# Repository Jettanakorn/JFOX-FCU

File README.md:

# JFOX FCU - Bare-Metal Rust Flight Controller

A bare-metal Rust firmware for the JFOX Flight Control Unit, targeting the
**PX4 FMUv2 board family** — `PX4FMUv2.4.5` and `Pixhawk 2.4.8` are revisions
of the same reference design and share this pin map.

**Verified on real Pixhawk 2.4.8 hardware (2026-08-04):** `jfox-fcu-usb`
flashes via QGroundControl, enumerates over USB, and QGC connects and holds the
link. Two things still vary across the family and are not settled by this
firmware — sensor population (2.4.8 clones may carry an ICM-20608/20602 rather
than an MPU-6000; `drivers::mpu6000` checks `WHO_AM_I` and fails loudly if so)
and silicon revision (which is why `memory.x` uses flash bank 1 only — see the
note there).

## Hardware

- **MCU**: STM32F427VIT6 (ARM Cortex-M4F @ 168MHz — see [Clock Configuration](#clock-configuration) for why not the part's 180MHz maximum)
- **Flash**: 2MB
- **RAM**: 256KB (192KB main + 64KB CCM)
- **IMU**: MPU-6000 (6-axis gyro + accel) @ 1kHz
- **Barometer**: MS5611
- **Storage**: FM25V01 FRAM (128Kbit)
- **Communication**: 4x UART, USB, CAN, I2C, SPI
- **I/O**: 8x PWM outputs

Schematic-level detail (connector pinouts, net traces) is in
**[`hardware/PX4FMUv2.4.5_NETS.md`](hardware/PX4FMUv2.4.5_NETS.md)**, derived
from the board's own Eagle netlist. The 3-board TMR array's KiCad project
lives in **[`hardware/`](hardware/README.md)**.

## Where things are

**Start here, depending on what you want to do:**

| I want to… | Read |
|---|---|
| Build firmware and get it onto a board | [`BUILD_AND_FLASH.md`](BUILD_AND_FLASH.md) |
| Bring up real hardware, 1 board → 3-board TMR | [`HARDWARE_BRINGUP.md`](HARDWARE_BRINGUP.md) |
| Work on the TMR schematic or carrier PCB | [`hardware/README.md`](hardware/README.md) |
| Understand the control law and its verification | [`docs/do178c/`](docs/do178c/) |
| Run the simulator | [`sitl/README.md`](sitl/README.md) |
| Know where a custom datalink would fit | [`JFOXGROUNDCONTROL_ROADMAP.md`](JFOXGROUNDCONTROL_ROADMAP.md) |

### Repository layout

```
jfox-fcu/
├── firmware/       # RTIC application - four [[bin]] targets, see BUILD_AND_FLASH.md
├── bsp/            # Board support: pin map, clock tree
├── hal/            # Register-level drivers: GPIO, SPI, UART, PWM, CAN, DWT
├── drivers/        # Sensors and storage: MPU-6000, FM25V01 FRAM
├── math/           # Vectors, quaternions, matrices, PID, filters
├── flight/         # Control law: fusion, stabilize, MPC, adaptive, redundancy, arming, BIT
├── telemetry/      # MAVLink v1 encoder
├── common/         # Types shared across crates without a dependency cycle
├── sitl/           # Host simulator - the real control chain against a 6-DOF plant
├── hardware/       # TMR schematic + carrier PCB (KiCad). Not built by cargo.
└── docs/
    ├── do178c/     # Requirements, traceability, coverage, coding standard
    ├── historical/ # Superseded 2025-12-30 docs and scripts - do not follow
    └── board-photos/
```

Two scripts live at the root because the flashing instructions call them
directly: `px4_flash_complete.py` (PX4-bootloader upload — the one with the
`GET_CRC` step the bootloader requires) and `px_mkfw.py` (vendored from PX4,
packages a `.bin` into the `.px4` format QGroundControl expects).

`memory.x` and `ccmram.x` are linker scripts; `Cargo.toml` is the workspace.

### Key Features

- **Pure bare-metal**: Direct register access, no HAL dependencies
- **RTIC framework**: Real-time task scheduling with zero-cost concurrency
- **Sensor fusion**: Madgwick AHRS filter @ 1kHz
- **Control loops**: Cascaded PID (attitude + rate) @ 500Hz
- **Safety**: Arming logic, failsafe, voltage monitoring

## Building

### Prerequisites

```bash
# Install Rust nightly
rustup default nightly
rustup target add thumbv7em-none-eabihf

# Install tools
cargo install probe-rs
```

### Build Firmware

```bash
cd firmware
cargo build --release
```

### Flash

```bash
# Via probe-rs (ST-Link/J-Link)
probe-rs run --chip STM32F427VITx \
  target/thumbv7em-none-eabihf/release/jfox-fcu

# Or use cargo alias
cargo rr
```

This project has more than one firmware binary (see `firmware/Cargo.toml`'s
`[[bin]]` entries) and a second flashing path (the board's built-in PX4
bootloader over USB, no debug probe needed) - see **[`BUILD_AND_FLASH.md`](BUILD_AND_FLASH.md)**
for the full picture, including current build/flash status per binary and
how to connect Mission Planner/QGroundControl.

## Task Architecture

| Task | Rate | Priority | Description |
|------|------|----------|-------------|
| `imu_task` | 1000 Hz | 3 (highest) | Read MPU-6000, run Madgwick filter |
| `control_task` | 500 Hz | 2 | Attitude/rate control with PID |
| `motor_task` | 400 Hz | 1 | PWM output to motors/servos |
| `heartbeat_task` | 1 Hz | 0 (idle) | Status LED blink |

## Clock Configuration

- **HSE**: 24MHz (external crystal)
- **PLL**: 24MHz / 12 × 168 / 2 = 168MHz
- **SYSCLK**: 168MHz
- **AHB (HCLK)**: 168MHz
- **APB1 (PCLK1)**: 42MHz
- **APB2 (PCLK2)**: 84MHz
- **USB 48MHz**: PLLQ = 336MHz VCO / 7 = 48MHz exactly

### Why 168MHz, not the part's 180MHz maximum

USB OTG FS needs 48MHz ±0.25%, and on STM32F42x/43x that clock can come
**only** from the main PLL's Q-output (PLL48CK). Unlike the F446/F469 and
F412/F413, this part has no `CK48MSEL` mux, so PLLSAI cannot feed USB.

180MHz needs a 360MHz VCO, and 360 has no integer PLLQ giving 48
(360/7.5). A 336MHz VCO does: 336/7 = 48 exactly, with PLLP=/2 giving
168MHz. Exact USB and 180MHz are mutually exclusive on this silicon, and
working USB was chosen over the extra 12MHz.

An earlier revision ran at 180MHz and tried to route PLLSAI to USB by
writing `CK48MSEL` at offset 0x90 — reserved space on this part, so the
write did nothing and USB ran from PLLQ at 360/7 ≈ 51.43MHz (7.1% fast).
Windows enumeration failed with "Configuration Descriptor Request Failed"
under a null VID/PID. `bsp/src/clocks.rs` carries the full note.

Anything clock-derived must be taken from `bsp::clocks` rather than
hardcoded — CAN bit timing and UART baud divisors in particular both
break silently if the clock tree moves and a stale literal is left behind.

## Memory Layout

- **Flash**: 0x08000000 - 0x081FFFFF (2MB)
- **RAM**: 0x20000000 - 0x2002FFFF (192KB)
- **CCMRAM**: 0x10000000 - 0x1000FFFF (64KB)
  - Core-Coupled Memory for zero wait-state access
  - Used for time-critical data (attitude, PID state)

## Sensor Configuration

### MPU-6000 (Primary IMU)
- **Interface**: SPI1 @ 5.625MHz
- **Gyro range**: ±2000 °/s
- **Accel range**: ±16g
- **Sample rate**: 1000 Hz
- **DLPF**: 184 Hz bandwidth

## Development Status

### ✅ Completed
- [x] Workspace structure and build system
- [x] Memory layout and clock configuration
- [x] GPIO and SPI HAL implementation
- [x] MPU-6000 driver with full initialization
- [x] Vector and quaternion math library
- [x] Madgwick AHRS sensor fusion
- [x] PID controller implementation
- [x] RTIC application with task scheduling
- [x] MAVLink v1 telemetry (`jfox-fcu-usb`: HEARTBEAT/SYS_STATUS/ATTITUDE,
      interim GCS bridge - see `BUILD_AND_FLASH.md`)

### 🚧 In Progress
- [ ] UART HAL for telemetry/GPS
- [ ] PWM output for motor control
- [ ] RC input (PPM/S.Bus/Spektrum)
- [ ] Motor mixer (quad/hexa/plane)

### 📋 Planned
- [ ] MS5611 barometer driver
- [ ] GPS integration (NMEA/UBX)
- [ ] Position hold and navigation
- [ ] DMA for efficient I/O
- [ ] Configuration storage in FRAM

## Pin Mapping

### SPI1 - MPU-6000
- SCK: PE13 (AF5)
- MISO: PE14 (AF5)
- MOSI: PE15 (AF5)
- CS: PC2 (GPIO)
- DRDY: PD15 (GPIO input)

### UART1 - Telemetry
- TX: PA9 (AF7)
- RX: PA10 (AF7)

### PWM Outputs
- CH1-4: TIM1 (PE9, PE11, PE13, PE14)
- CH5-8: TIM4 (PD12, PD13, PD14, PD15)

## Debugging

### View logs via defmt
```bash
probe-rs run --chip STM32F427VITx
```

### GDB debugging
```bash
# Terminal 1: Start GDB server
probe-rs gdb-server --chip STM32F427VITx

# Terminal 2: Connect GDB
arm-none-eabi-gdb target/thumbv7em-none-eabihf/release/jfox-fcu
(gdb) target remote :1337
(gdb) load
(gdb) continue
```

## Performance

| Metric | Target | Notes |
|--------|--------|-------|
| CPU usage | <60% | Leave headroom for future features |
| RAM usage | <128 KB | Half of available RAM |
| Flash usage | <1 MB | Half of available flash |
| IMU jitter | <1ms | Consistent 1kHz sampling |
| Control latency | <10ms | Sensor to motor output |

## Safety Features

1. **Pre-arm checks**: Sensor health, calibration valid
2. **Arming logic**: Explicit RC command required
3. **Failsafe**: RC loss → disarm or hold
4. **Low voltage**: Battery protection
5. **Watchdog**: Auto-reset on firmware hang
6. **Data validation**: CRC checks on sensor data

## License

MIT OR Apache-2.0

## Contributing

This is a reference implementation for bare-metal Rust flight controller development.
Contributions welcome!

## References

- [PX4 Autopilot](https://px4.io/)
- [Madgwick AHRS](https://x-io.co.uk/open-source-imu-and-ahrs-algorithms/)
- [RTIC Framework](https://rtic.rs/)
- [Embedded Rust Book](https://rust-embedded.github.io/book/)

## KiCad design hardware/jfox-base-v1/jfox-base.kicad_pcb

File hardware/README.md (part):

# hardware/ — TMR schematic work

Hardware design for the 3-board TMR array. Firmware lives everywhere else in
this repo; nothing here is compiled or linked into it.

## Why this directory exists

The only copy of the PX4FMUv2.4.5 schematic previously in this repo was
`docs/PX4FMUv2.4.5.pdf` — a vector PDF with **no extractable text**. Every
hardware fact taken from it had to be read off rendered page images by eye.
That is fine for orientation and bad as a foundation for a new board design.

The same design is published in machine-readable form: `PX4/Hardware`'s
`FMUv2/PX4FMUv2.4.5.sch`, Eagle 7.1.0 XML. The PDF is a plot of that file.
So connector pinouts and net membership are now **derived** from the netlist
rather than transcribed.

## Layout

| Path | What |
|---|---|
| `vendor/PX4FMUv2.4.5.sch` | Upstream Eagle source, unmodified. See `vendor/README.md`. |
| `tools/extract_eagle_nets.py` | Parses the above → `PX4FMUv2.4.5_NETS.md`. |
| `PX4FMUv2.4.5_NETS.md` | **Generated.** Connector/net reference. Do not hand-edit. |
| `tools/gen_tmr_schematic.py` | Emits the KiCad project below. |
| `jfox-tmr.kicad_pro` / `.kicad_sch` | **Generated.** Root: three FMU instances + carrier. |
| `fmu-v2/` | **Generated.** The real board, safe to instantiate 3x. |
| `carrier.kicad_sch` | **Generated.** The new carrier/backplane design. |
| `jfox.kicad_sym` / `sym-lib-table` | **Generated.** Connector symbols, registered as a project library. |
| `tools/check_tmr_netlist.py` | Asserts the redundancy invariants against KiCad's netlist. |
| `tools/gen_fmu_hierarchical.py` | Converts the import for safe 3× instantiation → `fmu-v2/`. |
| `tools/annotate_tmr_instances.py` | Gives each FMU instance its own reference designators. |
| `tools/check_fmu_conversion.py` | Proves the conversion changed no connectivity. |
| `tools/route_carrier.py` | Places the connectors and routes the carrier board. |

Full pipeline — regenerate and verify everything:

```bash
python hardware/tools/extract_eagle_nets.py
python hardware/tools/repair_import_hierarchy.py
python hardware/tools/gen_fmu_hierarchical.py
python hardware/tools/gen_tmr_schematic.py
python hardware/tools/annotate_tmr_instances.py
python hardware/tools/gen_carrier_pcb.py
#   ... then F8 in KiCad to load the netlist onto the board ...
python hardware/tools/route_carrier.py
python hardware/tools/check_fmu_conversion.py
python hardware/tools/check_tmr_netlist.py
```

Order matters: `annotate_tmr_instances.py` reads sheet UUIDs that
`gen_tmr_schematic.py` allocates, so it has to run after it.

(On this machine `python` on `PATH` is the Microsoft Store stub — use
`C:\Users\Jetta\AppData\Local\Programs\Python\Python312\python.exe`.)

## How to verify all of it

```bash
python hardware/tools/verify_all.py
```

Eight checks, each asking KiCad itself rather than the generators — the point
is to catch a generator that produced something plausible but wrong. Expect:

```
Imported FMU board
  [PASS] conversion preserved every connection  -- 262 nets in the import, 262 in the converted copy

3-board TMR system
  [PASS] every component has a unique designator  -- 885 instances, 885 distinct
  [PASS] the three supplies share no node
  [PASS] CAN_H reaches all three modules  -- via each module's own MAX3051
  [PASS] all three module terminators are on the bus  -- ['R409A', 'R409B', 'R409C']

Carrier board
  [PASS] DRC clean  -- 0 violations
  [PASS] fully routed  -- 0 unconnected
  [PASS] no net dead-ends on the board  -- 15 nets, all with a path across

all 8 checks passed
```

It exits non-zero on failure, and it is negative-tested: deleting a single
routed trace turns "fully routed" into `[FAIL] 1 unconnected`.

**Close KiCad before trusting a FAIL.** The script reads what is on disk; if
KiCad has unsaved changes the two disagree, and it prints a note when it sees
a lock file.

Everything here is saved in **KiCad 10** format. Each file type carries its own
version number — schematics `20260306`, boards `20260206`, symbol libraries
`20251024` — so those differing numbers are expected, not a mix of versions.
`gen_tmr_schematic.py` runs `kicad-cli sch upgrade` / `sym upgrade` on its
output, so opening the project does not rewrite anything.

### Looking at it by hand

| To see | Open |
|---|---|
| The board | `hardware/carrier/carrier.kicad_pro` → PCB editor |
| The carrier schematic | same project → schematic editor |
| The whole 3-board system | `hardware/jfox-tmr.kicad_pro` → schematic only |
| One module's real internals | `hardware/fmu-v2/fmu-v2.kicad_sch` (12 pages) |

In the TMR schematic, open the hierarchy navigator to move between `FMU-A`,
`FMU-B`, `FMU-C` and `CARRIER`. The three FMU sheets are the *same file* — a
change to one is a change to all three, which is the point.

## New board: JFOX-FMU v1

A ground-up replacement for the PX4FMUv2.4.5 modules - STM32H753 (Cortex-M7
@480 MHz, **1 MB RAM**), three IMUs per board, switchable CAN termination.
The v2.4.5 is a guideline only.

Specification: [`jfox-fmu-v1/ARCHITECTURE.md`](jfox-fmu-v1/ARCHITECTURE.md).
No schematic captured yet.

Note that the existing carrier PCB is built for v2.4.5's DF13 pinout and will
not fit the new module; it needs a redesign alongside. Its verified content -
CAN daisy chain, independent per-board power, no on-carrier termination -
carries over unchanged.

## Two projects, and why

| Project | What it is | Has a PCB? |
|---|---|---|
| `jfox-tmr.kicad_pro` | The **system** schematic — three FMU modules + the carrier, showing how the array is wired | **No, deliberately** |
| `carrier/carrier.kicad_pro` | The **board** — the only new hardware here | Yes |

Opening `jfox-tmr` and clicking **Switch to PCB Editor** pops up *"file does
not exist"* and offers to create one. **Say no.** That project has no board on
purpose: the three FMU modules are separately manufactured hardware, not parts
to be placed. A board made from that schematic would try to lay out ~885
components — three copies of a board that already exists. The same warning is
printed on the schematic's own root sheet.

The PCB is the carrier alone. Open `hardware/carrier/carrier.kicad_pro`.

## The TMR project

`jfox-tmr.kicad_sch` is the root. It instantiates **one** sheet file
(`fmu-v2/fmu-v2.kicad_sch`) three times as FMU-A/B/C — that is KiCad's own idiom for
identical repeated blocks, and it means editing the board design once edits
all three while KiCad still keeps their reference designators distinct via
per-instance paths.

Signal split, which is the load-bearing design decision:

- `CAN_H`, `CAN_L`, `GND`, `SAFETY` are **global labels** — correct precisely
  because all three boards genuinely share those nets.
- Power signals are **hierarchical pins**, so each board's stay
  separate. That separation is the entire point of board-level redundancy; a
  global label there would silently short all three supplies together.

That second point is the kind of mistake that looks fine in a schematic and
only shows up when hardware misbehaves, so it is checked mechanically.
`tools/check_tmr_netlist.py` runs `kicad-cli sch export netlist` and asserts,
against KiCad's own output:

- the three brick supplies share no node (independent power),
- `CAN_H`/`CAN_L` reach all three modules (one bus, not three stubs),
- **no resistor sits on CAN_H/CAN_L on the carrier** — each module already has
  a fixed 120Ω R409, and a fourth in parallel would make the bus worse,
- no net terminates on a single pin,
- `GND` is common across all modules.

Currently all five hold. Each check is negative-tested (deliberately merging
two supply nets, or dropping a module off the bus, both get caught).

## Status

**The Eagle import is done** (`PX4FMUv2.4.5/`) — 12 pages, 492 symbol
placements. Verified complete: the per-page symbol counts match an independent
parse of the Eagle source exactly, page for page
(23/36/24/32/49/69/45/49/58/24/49/34), and the exported netlist reproduces
`CAN_H`, `CAN_L`, `CAN1_TX` and `SAFETY` with the same nodes the Eagle netlist
has. No "Bus Entry needed" errors appeared.

**The import's root had to be repaired.** As it landed on disk, the container
root that referenced the 12 pages had been overwritten with page 1's own
content — its symbols carried instance path `/e0a7e50b…`, the UUID
`.kicad_pro` records as sheet `_1`, which is what a child page saved over its
parent looks like. KiCad consequently saw a **one-page project**: ERC
enumerated only `Sheet /`, and a netlist export returned 8 components instead
of ~292. The other 11 files were on disk, complete, and unreachable.

`tools/repair_import_hierarchy.py` rebuilds the container (moves page 1 to
`PX4FMUv2.4.5_1.kicad_sch`, writes a root holding the 12 sheet elements with
the UUIDs from `.kicad_pro` so existing instance paths still resolve) and then
verifies the result against the Eagle source. All 13 sheets now enumerate. Run
it again after any re-import; it is idempotent.

Note for anyone hand-editing these files: **instance-path forms differ between
KiCad versions and between these files.** KiCad 10 roots symbol paths at the
root document's UUID; KiCad 7 did not; the imported pages use a third form.
`annotate_tmr_instances.py` derives the prefix from the files rather than
assuming - assuming any one of them silently gave all three boards the same
reference designators.

### The global-label problem, and how it was fixed

The import represents every cross-page net as a **global** label — 136
distinct, 123 spanning multiple pages, no internal hierarchy at all. A global
label is global across the *whole project*, so instantiating this design three
times would have shorted all 120 non-shared nets together across FMU-A/B/C:
every SPI bus, every MCU pin, every internal rail. The schematic would have
looked completely normal and been electrically meaningless.

`tools/gen_fmu_hierarchical.py` generates `fmu-v2/` from the pristine import,
which it leaves untouched and re-importable:

- 120 multi-page nets → hierarchical labels plus matching sheet pins on a new
  container root, joined there by local labels. Connectivity is preserved but
  **scoped to one instance** of the board.
- 12 single-page nets → plain local labels; they never left the page.
- `CAN_H`, `CAN_L`, `GND`, `SAFETY` → left global, which is correct. They are
  the four nets the three modules genuinely share, and that is the same split
  the carrier assumes.
- `VDD_5V_BRICK`, `BATT_CURRENT_SENS`, `BATT_VOLTAGE_SENS` → also exposed on
  the root, so each board's power reaches its own carrier connector. (Those
  are the board's own net names; an earlier version of the TMR generator had
  invented `BATT_V_SENS`/`BATT_I_SENS`, which matched nothing.)

That is a lot of automated surgery on a design nobody can eyeball, so it is
checked rather than trusted. `tools/check_fmu_conversion.py` exports a netlist
from the pristine import and from the converted copy and compares them net by
net: **262 multi-pin nets on both sides, joining exactly the same pins.**

`tools/annotate_tmr_instances.py` then gives each instance its own reference
designators — `C101` becomes `C101A`/`C101B`/`C101C` — by writing one
`(path ...)` entry per instance, the same mechanism KiCad's own test project
uses for a thrice-instantiated subsheet. Without it all three boards report
the same designators and KiCad refuses to annotate.

## Installing KiCad

Current stable is **10.0.5** (released 2026-07-22). Install with:

```bash
winget install -e --id KiCad.KiCad
```

This is the x86-64 NSIS installer straight from KiCad's GitHub release.
Confirm it landed:

```bash
kicad-cli version
```

**Note the install location.** winget installs KiCad at *current-user* scope,
so it lands in `%LOCALAPPDATA%\Programs\KiCad\10.0\bin` — **not**
`C:\Program Files\KiCad`. Nothing is added to `PATH`, so either add that `bin`
directory or call the executable by full path.
`tools/check_tmr_netlist.py` probes both locations plus `PATH`.

**Why 10.x**, checked rather than assumed — KiCad 10's own docs list Eagle
(Autodesk) `.sch` XML, "Eagle version 6.x and later", among the supported
import formats, and `vendor/PX4FMUv2.4.5.sch` is Eagle 7.1.0. The docs also
confirm the importer extracts symbols from the file's embedded libraries into
a generated KiCad symbol library, which matches this file's seven embedded
libraries (`pixhawk2`, `con-hirose-df13`, `SparkFun`, …).

**Expect one Eagle-specific ERC violation.** KiCad documents a *"Bus Entry
needed"* error that "only applies to projects imported from EAGLE projects" —
places where the importer could not add bus entries automatically and you have
to place them by hand. Post-import cleanup, not a broken import.

**Verified with KiCad 10.0.5**: it parses all four files and resolves the
hierarchy — ERC enumerates `/`, `/FMU-A/`, `/FMU-B/`, `/FMU-C/` and
`/CARRIER/`, so the three-instance structure works. The netlist exports
cleanly and the invariants above hold.

ERC on the carrier reports **0 violations**. On the full TMR system it
reports 433, all inherited from the upstream board and its import - see
"System verification" above.

Two real defects were caught this way and fixed:

- **Symbol instance paths were wrong.** They used each child file's own UUID
  instead of `/<root-uuid>/<sheet-element-uuid>`. The files still parsed and
  the generator's structural checks still passed, but KiCad placed every
  carrier symbol on the root sheet. Only ERC surfaced it. The generator now
  checks instance-path rooting directly.
- **Symbols resolved to no registered library** (10 `lib_symbol_issues`
  warnings). Fixed by emitting a real `jfox.kicad_sym` plus a `sym-lib-table`.

## System verification

The whole point of the array is that three boards fail independently but vote
together. That is now demonstrable from KiCad's own netlist of
`jfox-tmr.kicad_sch`, not asserted:

- **885 component instances, 885 distinct references, 0 duplicated** — the
  three boards are genuinely separate instances, not one drawn three times.
- **The three supplies share no node.** `/VBRICK_A` reaches `C1101A`,
  `U1101A`, `J601A` and carrier `J4`/`J7`; `/VBRICK_B` reaches the `B` parts
  and `J5`/`J8`; `/VBRICK_C` the `C` parts and `J6`/`J9`. One brick failing
  cannot take the other two boards down.
- **CAN_H is one bus reaching all three modules' real hardware** — `U401A`,
  `U401B`, `U401C` (the MAX3051 transceivers), `R409A/B/C` (their fixed
  terminators), `J405A/B/C`, and the carrier's `J1`/`J2`/`J3`.

That last line is also the clearest statement of the R409 problem: three
terminators really are on one bus, so one of them really does have to come
off.

ERC on the full system reports **433 violations**, down from 1639 before the
conversion and library fixes. What remains is inherited from the upstream
board and its import, not introduced here: 363 `footprint_link_issues` (the
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
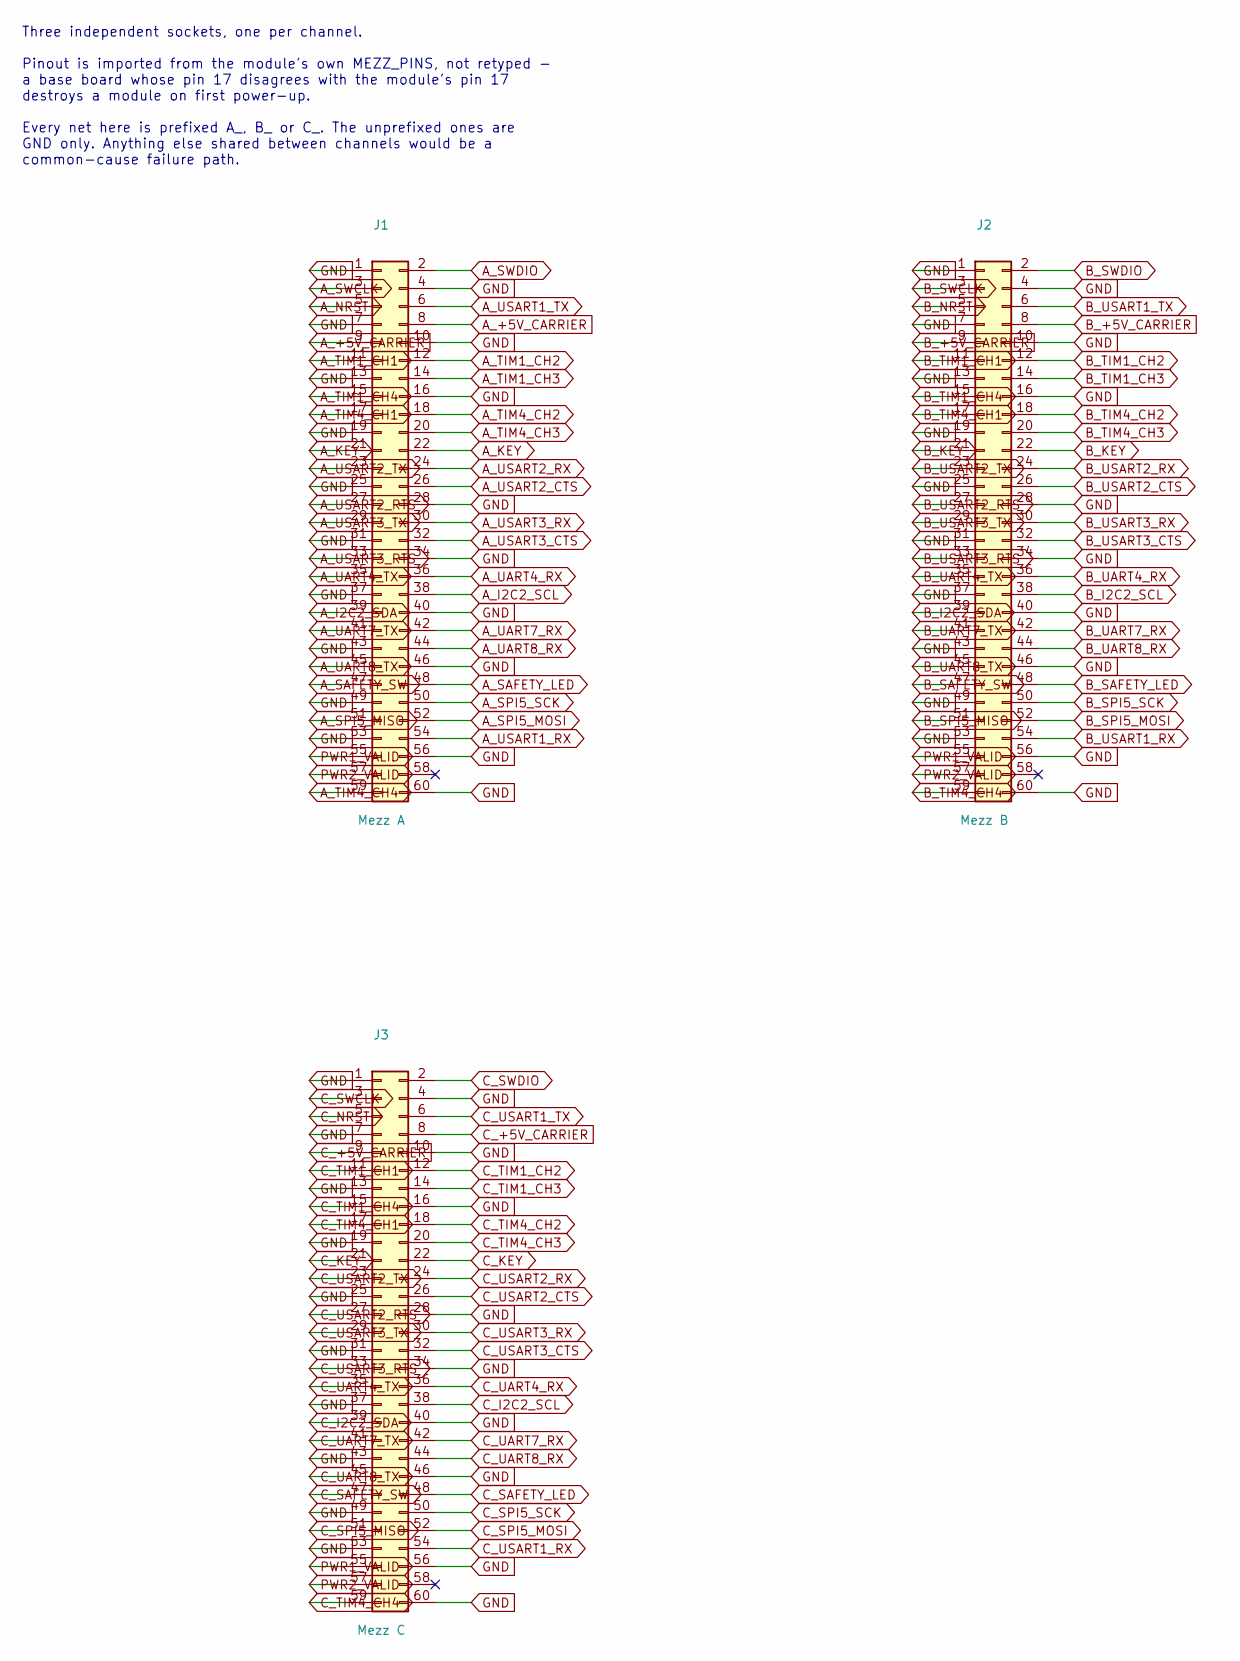
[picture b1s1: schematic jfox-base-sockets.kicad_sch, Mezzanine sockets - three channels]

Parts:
J1: Mezz A; Samtec_MECF-30-01-L-DV_2x30_P1.27mm_Polarized_Socket_Horizo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
J2: Mezz B; Samtec_MECF-30-01-L-DV_2x30_P1.27mm_Polarized_Socket_Horizo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
J3: Mezz C; Samtec_MECF-30-01-L-DV_2x30_P1.27mm_Polarized_Socket_Horizo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

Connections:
A_+5V_CARRIER: J1.8, J1.9; also elsewhere on the board
A_I2C2_SCL: J1.38; also elsewhere on the board
A_I2C2_SDA: J1.39; also elsewhere on the board
A_NRST: J1.5; also elsewhere on the board
A_SAFETY_LED: J1.48; also elsewhere on the board
A_SAFETY_SW: J1.47; also elsewhere on the board
A_SPI5_MISO: J1.51; also elsewhere on the board
A_SPI5_MOSI: J1.52; also elsewhere on the board
A_SPI5_SCK: J1.50; also elsewhere on the board
A_SWCLK: J1.3; also elsewhere on the board
A_SWDIO: J1.2; also elsewhere on the board
A_TIM1_CH1: J1.11; also elsewhere on the board
A_TIM1_CH2: J1.12; also elsewhere on the board
A_TIM1_CH3: J1.14; also elsewhere on the board
A_TIM1_CH4: J1.15; also elsewhere on the board
A_TIM4_CH1: J1.17; also elsewhere on the board
A_TIM4_CH2: J1.18; also elsewhere on the board
A_TIM4_CH3: J1.20; also elsewhere on the board
A_TIM4_CH4: J1.59; also elsewhere on the board
A_UART4_RX: J1.36; also elsewhere on the board
A_UART4_TX: J1.35; also elsewhere on the board
A_UART7_RX: J1.42; also elsewhere on the board
A_UART7_TX: J1.41; also elsewhere on the board
A_UART8_RX: J1.44; also elsewhere on the board
A_UART8_TX: J1.45; also elsewhere on the board
A_USART1_RX: J1.54; also elsewhere on the board
A_USART1_TX: J1.6; also elsewhere on the board
A_USART2_CTS: J1.26; also elsewhere on the board
A_USART2_RTS: J1.27; also elsewhere on the board
A_USART2_RX: J1.24; also elsewhere on the board
A_USART2_TX: J1.23; also elsewhere on the board
A_USART3_CTS: J1.32; also elsewhere on the board
A_USART3_RTS: J1.33; also elsewhere on the board
A_USART3_RX: J1.30; also elsewhere on the board
A_USART3_TX: J1.29; also elsewhere on the board
B_+5V_CARRIER: J2.8, J2.9; also elsewhere on the board
B_I2C2_SCL: J2.38; also elsewhere on the board
B_I2C2_SDA: J2.39; also elsewhere on the board
B_NRST: J2.5; also elsewhere on the board
B_SAFETY_LED: J2.48; also elsewhere on the board
B_SAFETY_SW: J2.47; also elsewhere on the board
B_SPI5_MISO: J2.51; also elsewhere on the board
B_SPI5_MOSI: J2.52
B_SPI5_SCK: J2.50; also elsewhere on the board
B_SWCLK: J2.3; also elsewhere on the board
B_SWDIO: J2.2; also elsewhere on the board
B_TIM1_CH1: J2.11; also elsewhere on the board
B_TIM1_CH2: J2.12; also elsewhere on the board
B_TIM1_CH3: J2.14; also elsewhere on the board
B_TIM1_CH4: J2.15; also elsewhere on the board
B_TIM4_CH1: J2.17; also elsewhere on the board
B_TIM4_CH2: J2.18; also elsewhere on the board
B_TIM4_CH3: J2.20; also elsewhere on the board
B_TIM4_CH4: J2.59; also elsewhere on the board
B_UART4_RX: J2.36; also elsewhere on the board
B_UART4_TX: J2.35; also elsewhere on the board
B_UART7_RX: J2.42; also elsewhere on the board
B_UART7_TX: J2.41; also elsewhere on the board
B_UART8_RX: J2.44; also elsewhere on the board
B_UART8_TX: J2.45; also elsewhere on the board
B_USART1_RX: J2.54
B_USART1_TX: J2.6; also elsewhere on the board
B_USART2_CTS: J2.26; also elsewhere on the board
B_USART2_RTS: J2.27; also elsewhere on the board
B_USART2_RX: J2.24; also elsewhere on the board
B_USART2_TX: J2.23; also elsewhere on the board
B_USART3_CTS: J2.32; also elsewhere on the board
B_USART3_RTS: J2.33; also elsewhere on the board
B_USART3_RX: J2.30; also elsewhere on the board
B_USART3_TX: J2.29; also elsewhere on the board
C_+5V_CARRIER: J3.8, J3.9; also elsewhere on the board
C_I2C2_SCL: J3.38; also elsewhere on the board
C_I2C2_SDA: J3.39; also elsewhere on the board
C_NRST: J3.5; also elsewhere on the board
C_SAFETY_LED: J3.48; also elsewhere on the board
C_SAFETY_SW: J3.47; also elsewhere on the board
C_SPI5_MISO: J3.51; also elsewhere on the board
C_SPI5_MOSI: J3.52
C_SPI5_SCK: J3.50; also elsewhere on the board
C_SWCLK: J3.3; also elsewhere on the board
C_SWDIO: J3.2; also elsewhere on the board
C_TIM1_CH1: J3.11; also elsewhere on the board
C_TIM1_CH2: J3.12; also elsewhere on the board
C_TIM1_CH3: J3.14; also elsewhere on the board
C_TIM1_CH4: J3.15; also elsewhere on the board
C_TIM4_CH1: J3.17; also elsewhere on the board
C_TIM4_CH2: J3.18; also elsewhere on the board
C_TIM4_CH3: J3.20; also elsewhere on the board
C_TIM4_CH4: J3.59; also elsewhere on the board
C_UART4_RX: J3.36; also elsewhere on the board
C_UART4_TX: J3.35; also elsewhere on the board
C_UART7_RX: J3.42; also elsewhere on the board
C_UART7_TX: J3.41; also elsewhere on the board
C_UART8_RX: J3.44; also elsewhere on the board
C_UART8_TX: J3.45; also elsewhere on the board
C_USART1_RX: J3.54
C_USART1_TX: J3.6; also elsewhere on the board
C_USART2_CTS: J3.26; also elsewhere on the board
C_USART2_RTS: J3.27; also elsewhere on the board
C_USART2_RX: J3.24; also elsewhere on the board
C_USART2_TX: J3.23; also elsewhere on the board
C_USART3_CTS: J3.32; also elsewhere on the board
C_USART3_RTS: J3.33; also elsewhere on the board
C_USART3_RX: J3.30; also elsewhere on the board
C_USART3_TX: J3.29; also elsewhere on the board
GND: J1.1, J1.4, J1.7, J1.10, J1.13, J1.16, J1.19, J1.25, J1.28, J1.31, J1.34, J1.37, J1.40, J1.43, J1.46, J1.49, J1.53, J1.56, J1.60, J2.1, J2.4, J2.7, J2.10, J2.13, J2.16, J2.19, J2.25, J2.28, J2.31, J2.34, J2.37, J2.40, J2.43, J2.46, J2.49, J2.53, J2.56, J2.60, J3.1, J3.4, J3.7, J3.10, J3.13, J3.16, J3.19, J3.25, J3.28, J3.31, J3.34, J3.37, J3.40, J3.43, J3.46, J3.49, J3.53, J3.56, J3.60; also elsewhere on the board
PWR1_VALID: J1.55, J2.55, J3.55; also elsewhere on the board
PWR2_VALID: J1.57, J2.57, J3.57; also elsewhere on the board

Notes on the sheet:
Three independent sockets, one per channel. Pinout is imported from the module's own MEZZ_PINS, not retyped - a base board whose pin 17 disagrees with the module's pin 17 destroys a module on first power-up. Every net here is prefixed A_, B_ or C_. The unprefixed ones are GND only. Anything else sh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

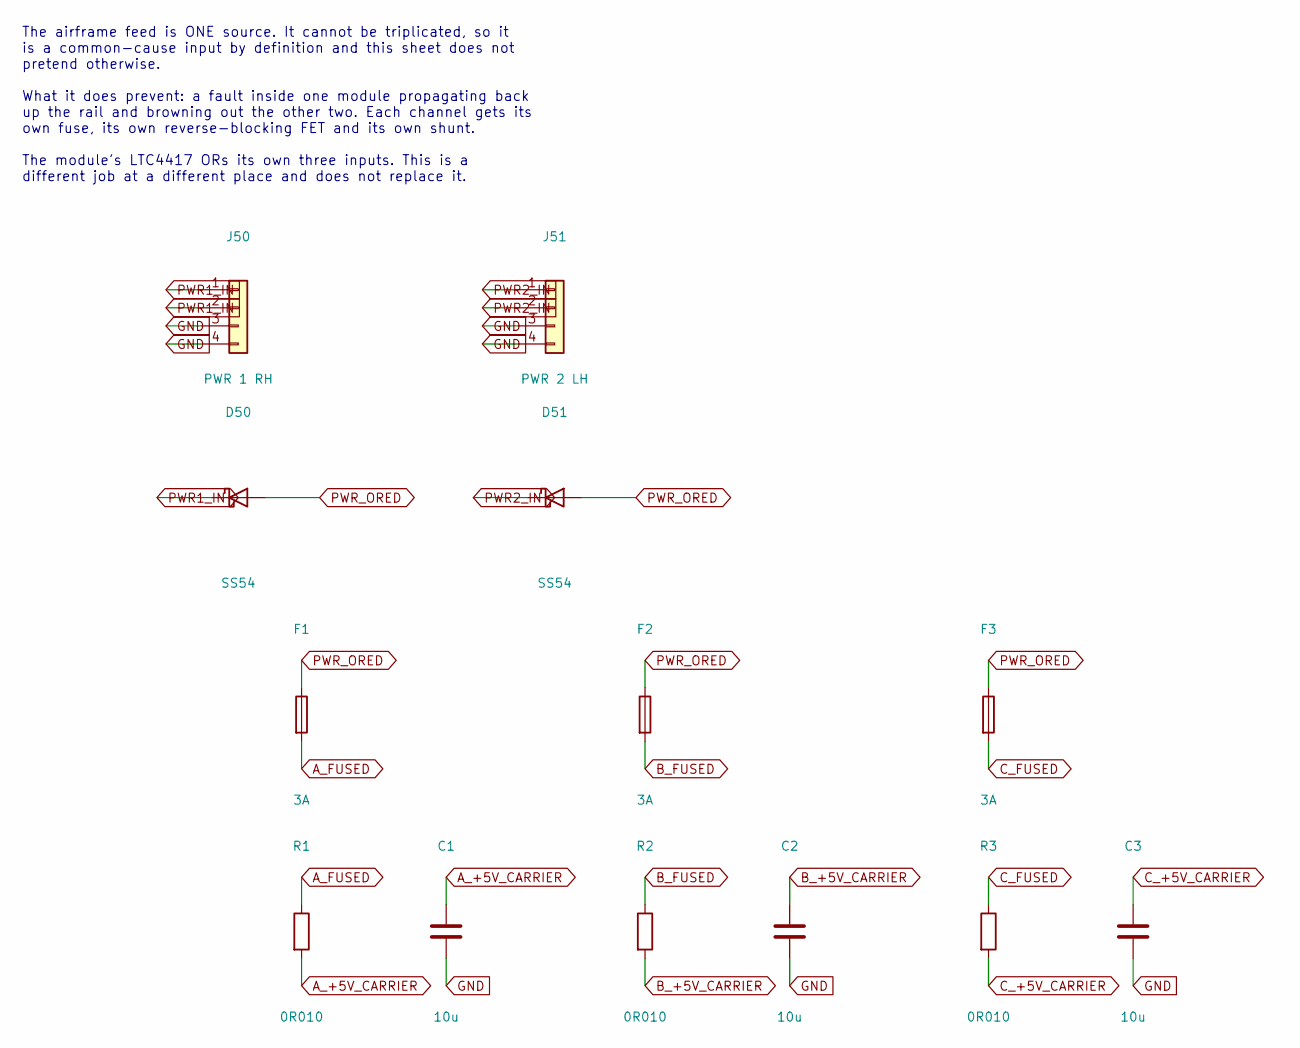
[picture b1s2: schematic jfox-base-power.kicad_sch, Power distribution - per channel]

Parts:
C1, C2, C3: 10u; C_0805_2012Metric
D50, D51: SS54; D_SMA
F1, F2, F3: 3A; Fuse_1206_3216Metric
J50: PWR 1 RH; JST_GH_SM04B-GHS-TB_1x04-1MP_P1.25mm_Horizontal
J51: PWR 2 LH; JST_GH_SM04B-GHS-TB_1x04-1MP_P1.25mm_Horizontal
R1, R2, R3: 0R010; R_0402_1005Metric

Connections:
A_+5V_CARRIER: C1.1, R1.2; also elsewhere on the board
A_FUSED: F1.2, R1.1
B_+5V_CARRIER: C2.1, R2.2; also elsewhere on the board
B_FUSED: F2.2, R2.1
C_+5V_CARRIER: C3.1, R3.2; also elsewhere on the board
C_FUSED: F3.2, R3.1
GND: C1.2, C2.2, C3.2, J50.3, J50.4, J51.3, J51.4; also elsewhere on the board
PWR_ORED: D50.2 (A), D51.2 (A), F1.1, F2.1, F3.1; also elsewhere on the board

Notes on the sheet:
The airframe feed is ONE source. It cannot be triplicated, so it is a common-cause input by definition and this sheet does not pretend otherwise. What it does prevent: a fault inside one module propagating back up the rail and browning out the other two. Each channel gets its own fuse, its own reve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

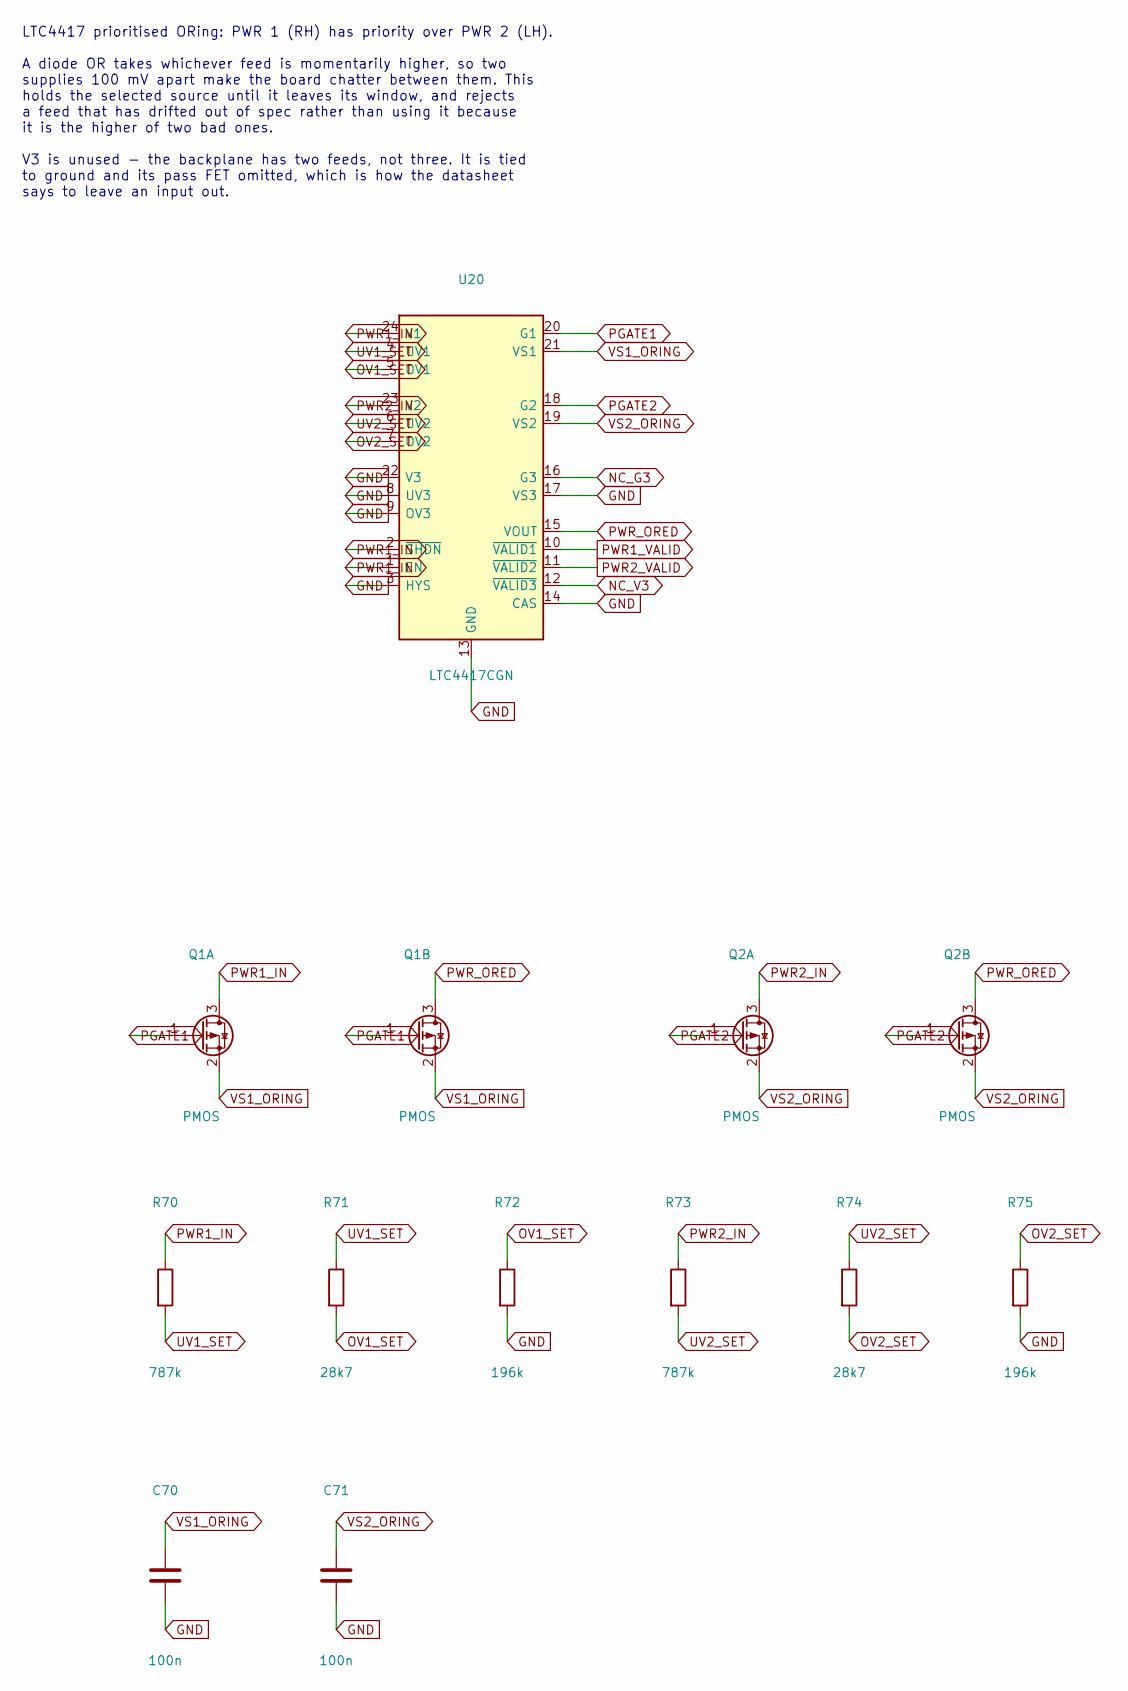
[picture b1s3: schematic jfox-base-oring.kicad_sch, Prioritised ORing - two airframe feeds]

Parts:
C70, C71: 100n; C_0402_1005Metric
Q1A, Q1B, Q2A, Q2B: PMOS; SOT-23
R70, R73: 787k; R_0402_1005Metric
R71, R74: 28k7; R_0402_1005Metric
R72, R75: 196k; R_0402_1005Metric
U20: LTC4417CGN; SSOP-24_3.9x8.7mm_P0.635mm

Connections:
GND: C70.2, C71.2, R72.2, R75.2, U20.3 (HYS), U20.8 (UV3), U20.9 (OV3), U20.13 (GND), U20.14 (CAS), U20.17 (VS3), U20.22 (V3); also elsewhere on the board
NC_G3: U20.16 (G3)
NC_V3: U20.12 (~VALID3)
OV1_SET: R71.2, R72.1, U20.5 (OV1)
OV2_SET: R74.2, R75.1, U20.7 (OV2)
PGATE1: Q1A.1 (G), Q1B.1 (G), U20.20 (G1)
PGATE2: Q2A.1 (G), Q2B.1 (G), U20.18 (G2)
PWR1_VALID: U20.10 (~VALID1); also elsewhere on the board
PWR2_VALID: U20.11 (~VALID2); also elsewhere on the board
PWR_ORED: Q1B.3 (D), Q2B.3 (D), U20.15 (VOUT); also elsewhere on the board
UV1_SET: R70.2, R71.1, U20.4 (UV1)
UV2_SET: R73.2, R74.1, U20.6 (UV2)
VS1_ORING: C70.1, Q1A.2 (S), Q1B.2 (S), U20.21 (VS1)
VS2_ORING: C71.1, Q2A.2 (S), Q2B.2 (S), U20.19 (VS2)

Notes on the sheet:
LTC4417 prioritised ORing: PWR 1 (RH) has priority over PWR 2 (LH). A diode OR takes whichever feed is momentarily higher, so two supplies 100 mV apart make the board chatter between them. This holds the selected source until it leaves its window, and rejects a feed that has drifted out of spec rat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

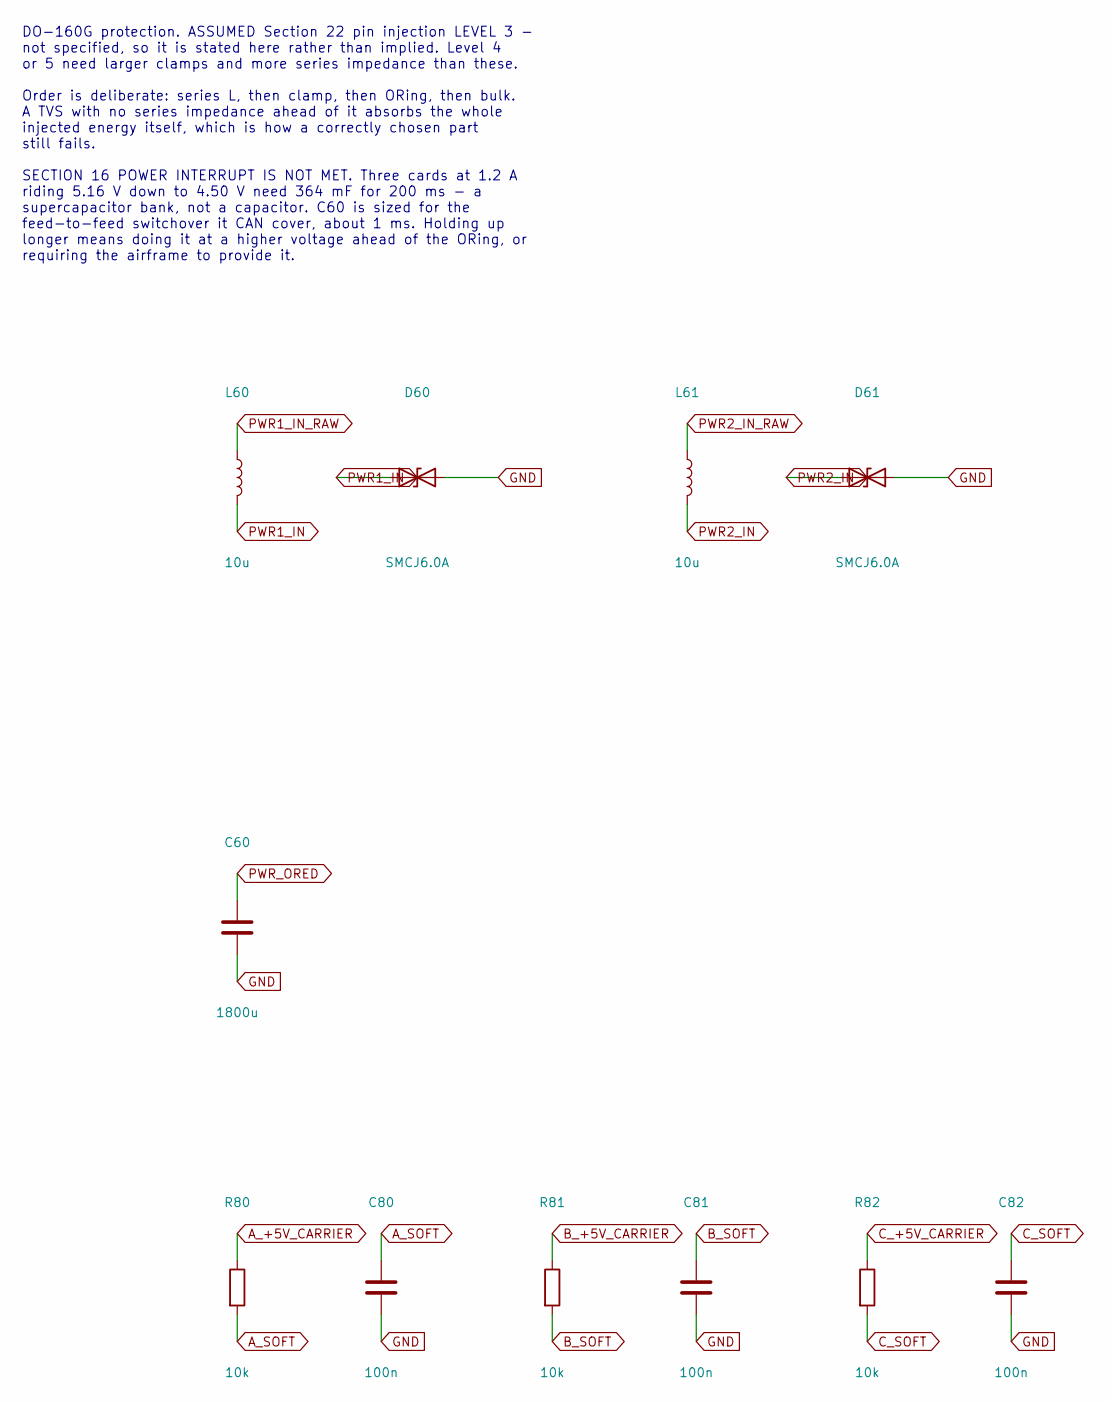
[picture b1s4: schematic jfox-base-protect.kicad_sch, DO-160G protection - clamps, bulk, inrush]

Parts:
C60: 1800u; C_0402_1005Metric
C80, C81, C82: 100n; C_0402_1005Metric
D60, D61: SMCJ6.0A; D_SMC
L60, L61: 10u; L_Bourns-SRN6045
R80, R81, R82: 10k; R_0402_1005Metric

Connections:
A_+5V_CARRIER: R80.1; also elsewhere on the board
A_SOFT: C80.1, R80.2
B_+5V_CARRIER: R81.1; also elsewhere on the board
B_SOFT: C81.1, R81.2
C_+5V_CARRIER: R82.1; also elsewhere on the board
C_SOFT: C82.1, R82.2
GND: C60.2, C80.2, C81.2, C82.2, D60.2 (A2), D61.2 (A2); also elsewhere on the board
PWR_ORED: C60.1; also elsewhere on the board

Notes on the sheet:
DO-160G protection. ASSUMED Section 22 pin injection LEVEL 3 - not specified, so it is stated here rather than implied. Level 4 or 5 need larger clamps and more series impedance than these. Order is deliberate: series L, then clamp, then ORing, then bulk. A TVS with no series impedance ahead of it 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

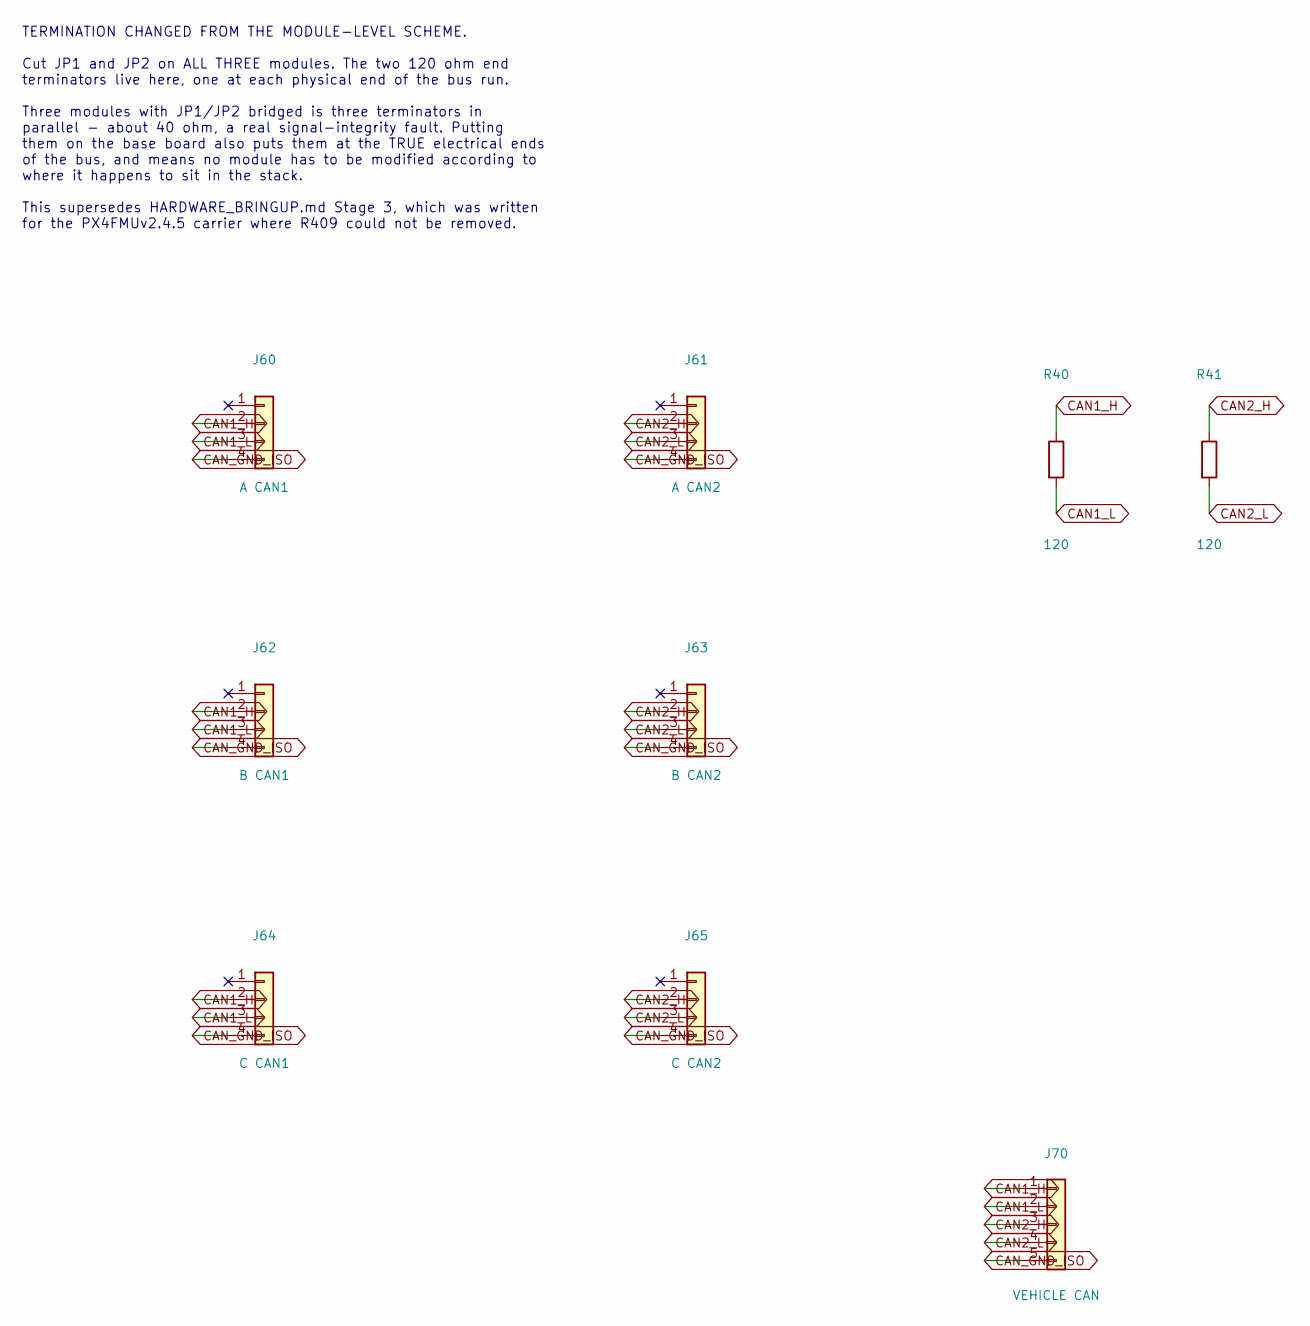
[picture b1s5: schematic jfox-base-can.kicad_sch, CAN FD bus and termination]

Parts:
J60: A CAN1; JST_GH_SM04B-GHS-TB_1x04-1MP_P1.25mm_Horizontal
J61: A CAN2; JST_GH_SM04B-GHS-TB_1x04-1MP_P1.25mm_Horizontal
J62: B CAN1; JST_GH_SM04B-GHS-TB_1x04-1MP_P1.25mm_Horizontal
J63: B CAN2; JST_GH_SM04B-GHS-TB_1x04-1MP_P1.25mm_Horizontal
J64: C CAN1; JST_GH_SM04B-GHS-TB_1x04-1MP_P1.25mm_Horizontal
J65: C CAN2; JST_GH_SM04B-GHS-TB_1x04-1MP_P1.25mm_Horizontal
J70: VEHICLE CAN; JST_GH_SM05B-GHS-TB_1x05-1MP_P1.25mm_Horizontal
R40, R41: 120; R_0402_1005Metric

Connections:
CAN1_H: J60.2, J62.2, J64.2, J70.1, R40.1
CAN1_L: J60.3, J62.3, J64.3, J70.2, R40.2
CAN2_H: J61.2, J63.2, J65.2, J70.3, R41.1
CAN2_L: J61.3, J63.3, J65.3, J70.4, R41.2
CAN_GND_ISO: J60.4, J61.4, J62.4, J63.4, J64.4, J65.4, J70.5

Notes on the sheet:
TERMINATION CHANGED FROM THE MODULE-LEVEL SCHEME. Cut JP1 and JP2 on ALL THREE modules. The two 120 ohm end terminators live here, one at each physical end of the bus run. Three modules with JP1/JP2 bridged is three terminators in parallel - about 40 ohm, a real signal-integrity fault. Putting them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

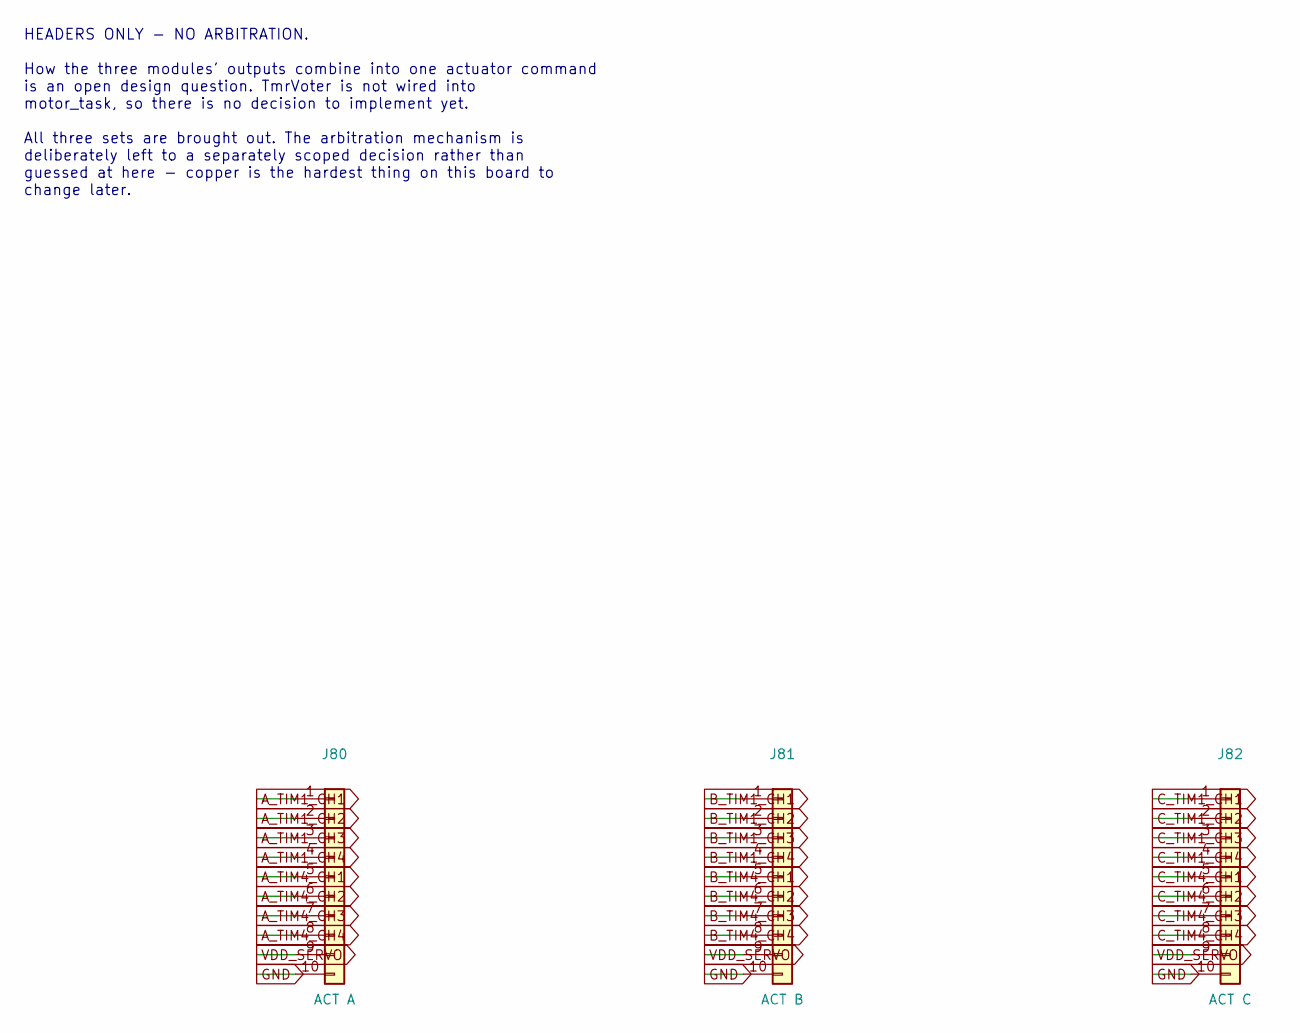
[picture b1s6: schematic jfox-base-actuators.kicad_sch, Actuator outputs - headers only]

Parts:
J80: ACT A; JST_GH_SM10B-GHS-TB_1x10-1MP_P1.25mm_Horizontal
J81: ACT B; JST_GH_SM10B-GHS-TB_1x10-1MP_P1.25mm_Horizontal
J82: ACT C; JST_GH_SM10B-GHS-TB_1x10-1MP_P1.25mm_Horizontal

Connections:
A_TIM1_CH1: J80.1; also elsewhere on the board
A_TIM1_CH2: J80.2; also elsewhere on the board
A_TIM1_CH3: J80.3; also elsewhere on the board
A_TIM1_CH4: J80.4; also elsewhere on the board
A_TIM4_CH1: J80.5; also elsewhere on the board
A_TIM4_CH2: J80.6; also elsewhere on the board
A_TIM4_CH3: J80.7; also elsewhere on the board
A_TIM4_CH4: J80.8; also elsewhere on the board
B_TIM1_CH1: J81.1; also elsewhere on the board
B_TIM1_CH2: J81.2; also elsewhere on the board
B_TIM1_CH3: J81.3; also elsewhere on the board
B_TIM1_CH4: J81.4; also elsewhere on the board
B_TIM4_CH1: J81.5; also elsewhere on the board
B_TIM4_CH2: J81.6; also elsewhere on the board
B_TIM4_CH3: J81.7; also elsewhere on the board
B_TIM4_CH4: J81.8; also elsewhere on the board
C_TIM1_CH1: J82.1; also elsewhere on the board
C_TIM1_CH2: J82.2; also elsewhere on the board
C_TIM1_CH3: J82.3; also elsewhere on the board
C_TIM1_CH4: J82.4; also elsewhere on the board
C_TIM4_CH1: J82.5; also elsewhere on the board
C_TIM4_CH2: J82.6; also elsewhere on the board
C_TIM4_CH3: J82.7; also elsewhere on the board
C_TIM4_CH4: J82.8; also elsewhere on the board
GND: J80.10, J81.10, J82.10; also elsewhere on the board
VDD_SERVO: J80.9, J81.9, J82.9

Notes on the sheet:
HEADERS ONLY - NO ARBITRATION. How the three modules' outputs combine into one actuator command is an open design question. TmrVoter is not wired into motor_task, so there is no decision to implement yet. All three sets are brought out. The arbitration mechanism is deliberately left to a separately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

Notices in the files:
hardware/README.md:
Licensing:
`vendor/PX4FMUv2.4.5.sch` is **CC BY-SA 3.0** from the Pixhawk project.
Share-alike propagates to derivative designs. A carrier board that *embeds
converted FMU sheets is a derivative; one drawn against only the connector
pinouts is a much weaker claim. Worth a lawyer's read before this ships as
part of a commercial product — see `vendor/README.md` for the attribution.
